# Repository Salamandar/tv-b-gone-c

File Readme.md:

# TV-B-Gone-C

This is a compact USB-C powered TV-B-Gone.

See <https://www.tvbgone.com> for details.

Thank you Mitch Altman for this amazing project!

## Flashing

It is suggested to use an Arduino as ISP.

Burn the FUSE bits for the external 8MHz oscillator option:
```
avrdude -cavrisp -b 19200 -P /dev/ttyUSB0 -pattiny85 -U lfuse:w:0xfe:m -U hfuse:w:0xdf:m -U efuse:w:0xff:m
```

Then flash the firmware:
```
avrdude -cavrisp -b 19200 -P /dev/ttyUSB0 -pattiny85 -U flash:w:tvbgone.hex
```

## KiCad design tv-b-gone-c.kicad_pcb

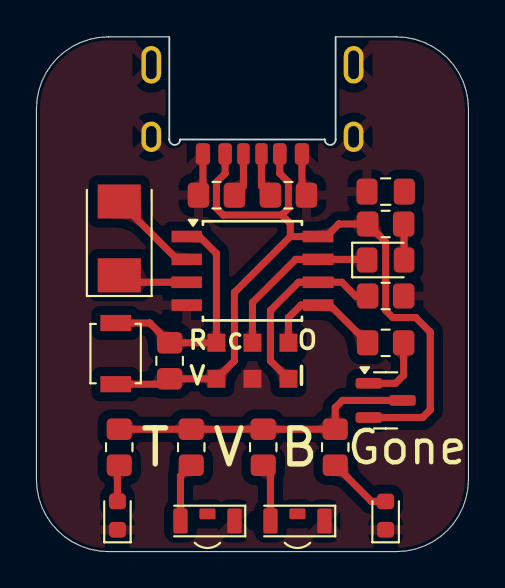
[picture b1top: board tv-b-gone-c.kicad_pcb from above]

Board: 2 copper layers, 24.0 x 28.6 mm, 27 parts (0 on the bottom side), 17 nets.

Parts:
C1: 100n; C_0805_2012Metric_Pad1.18x1.45mm_HandSolder
D1: D; LED_0805_2012Metric_Pad1.15x1.40mm_HandSolder
D2, D5: LED; LED_Wurth_15411494AA570
D3, D4: LED; LED_0603_1608Metric
J2: USB4515; USB4515-GF-A
Q5: MMBT2907A; SOT-23
R1, R7, R8, R9, R10: 100; R_0805_2012Metric_Pad1.20x1.40mm_HandSolder
R2, R4: 10k; R_0805_2012Metric_Pad1.20x1.40mm_HandSolder
R3: min. 680; R_0805_2012Metric_Pad1.20x1.40mm_HandSolder
R5, R6: 5k1; R_0805_2012Metric_Pad1.20x1.40mm_HandSolder
SW1: SW_SPST; SW_SPST_B3U-1000P
TP1: MOSI; TestPoint_Pad_1.0x1.0mm
TP2: MISO; TestPoint_Pad_1.0x1.0mm
TP3: SCK; TestPoint_Pad_1.0x1.0mm
TP4: ~{RST}; TestPoint_Pad_1.0x1.0mm
TP5: 5V; TestPoint_Pad_1.0x1.0mm
TP6: GND; TestPoint_Pad_1.0x1.0mm
U1: ATtiny85V-10S; SOIC-8W_5.3x5.3mm_P1.27mm
Y1: 8MHz; Crystal_SMD_Abracon_ABM3-2Pin_5.0x3.2mm

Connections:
+5V: C1.1, J2.A9 (VBUS), J2.B9 (VBUS), Q5.2 (E), R3.1, R4.1, SW1.1 (A), TP5.1, U1.8 (VCC)
/MISO: R2.1, TP2.1, U1.6 (PB1)
/MOSI_LEDs: R1.1, TP1.1, U1.5 (AREF/PB0)
/SCK_LED: D1.1 (K), TP3.1, U1.7 (PB2)
/~RST: R4.2, SW1.2 (B), TP4.1, U1.1 (~RESET/PB5)
GND: C1.2, D2.1 (K), D3.1 (K), D4.1 (K), D5.1 (K), J2.A12 (GND), J2.B12 (GND), J2.S1 (SHIELD), R2.2, R5.2, R6.2, TP6.1, U1.4 (GND)
unnamed: D1.2 (A), R3.2
unnamed: D2.2 (A), R8.1
unnamed: D3.2 (A), R7.1
unnamed: D4.2 (A), R10.1
unnamed: D5.2 (A), R9.1
unnamed: J2.A5 (CC1), R6.1
unnamed: J2.B5 (CC2), R5.1
unnamed: Q5.1 (B), R1.2
unnamed: Q5.3 (C), R7.2, R8.2, R9.2, R10.2
unnamed: U1.2 (XTAL1/PB3), Y1.2
unnamed: U1.3 (XTAL2/PB4), Y1.1

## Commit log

2024-12-11 Add gitignore
2024-12-18 Update values post-fab, fix trace
2024-12-19 Add readme with flash commands
2025-11-02 Add reset button, use mosfet
